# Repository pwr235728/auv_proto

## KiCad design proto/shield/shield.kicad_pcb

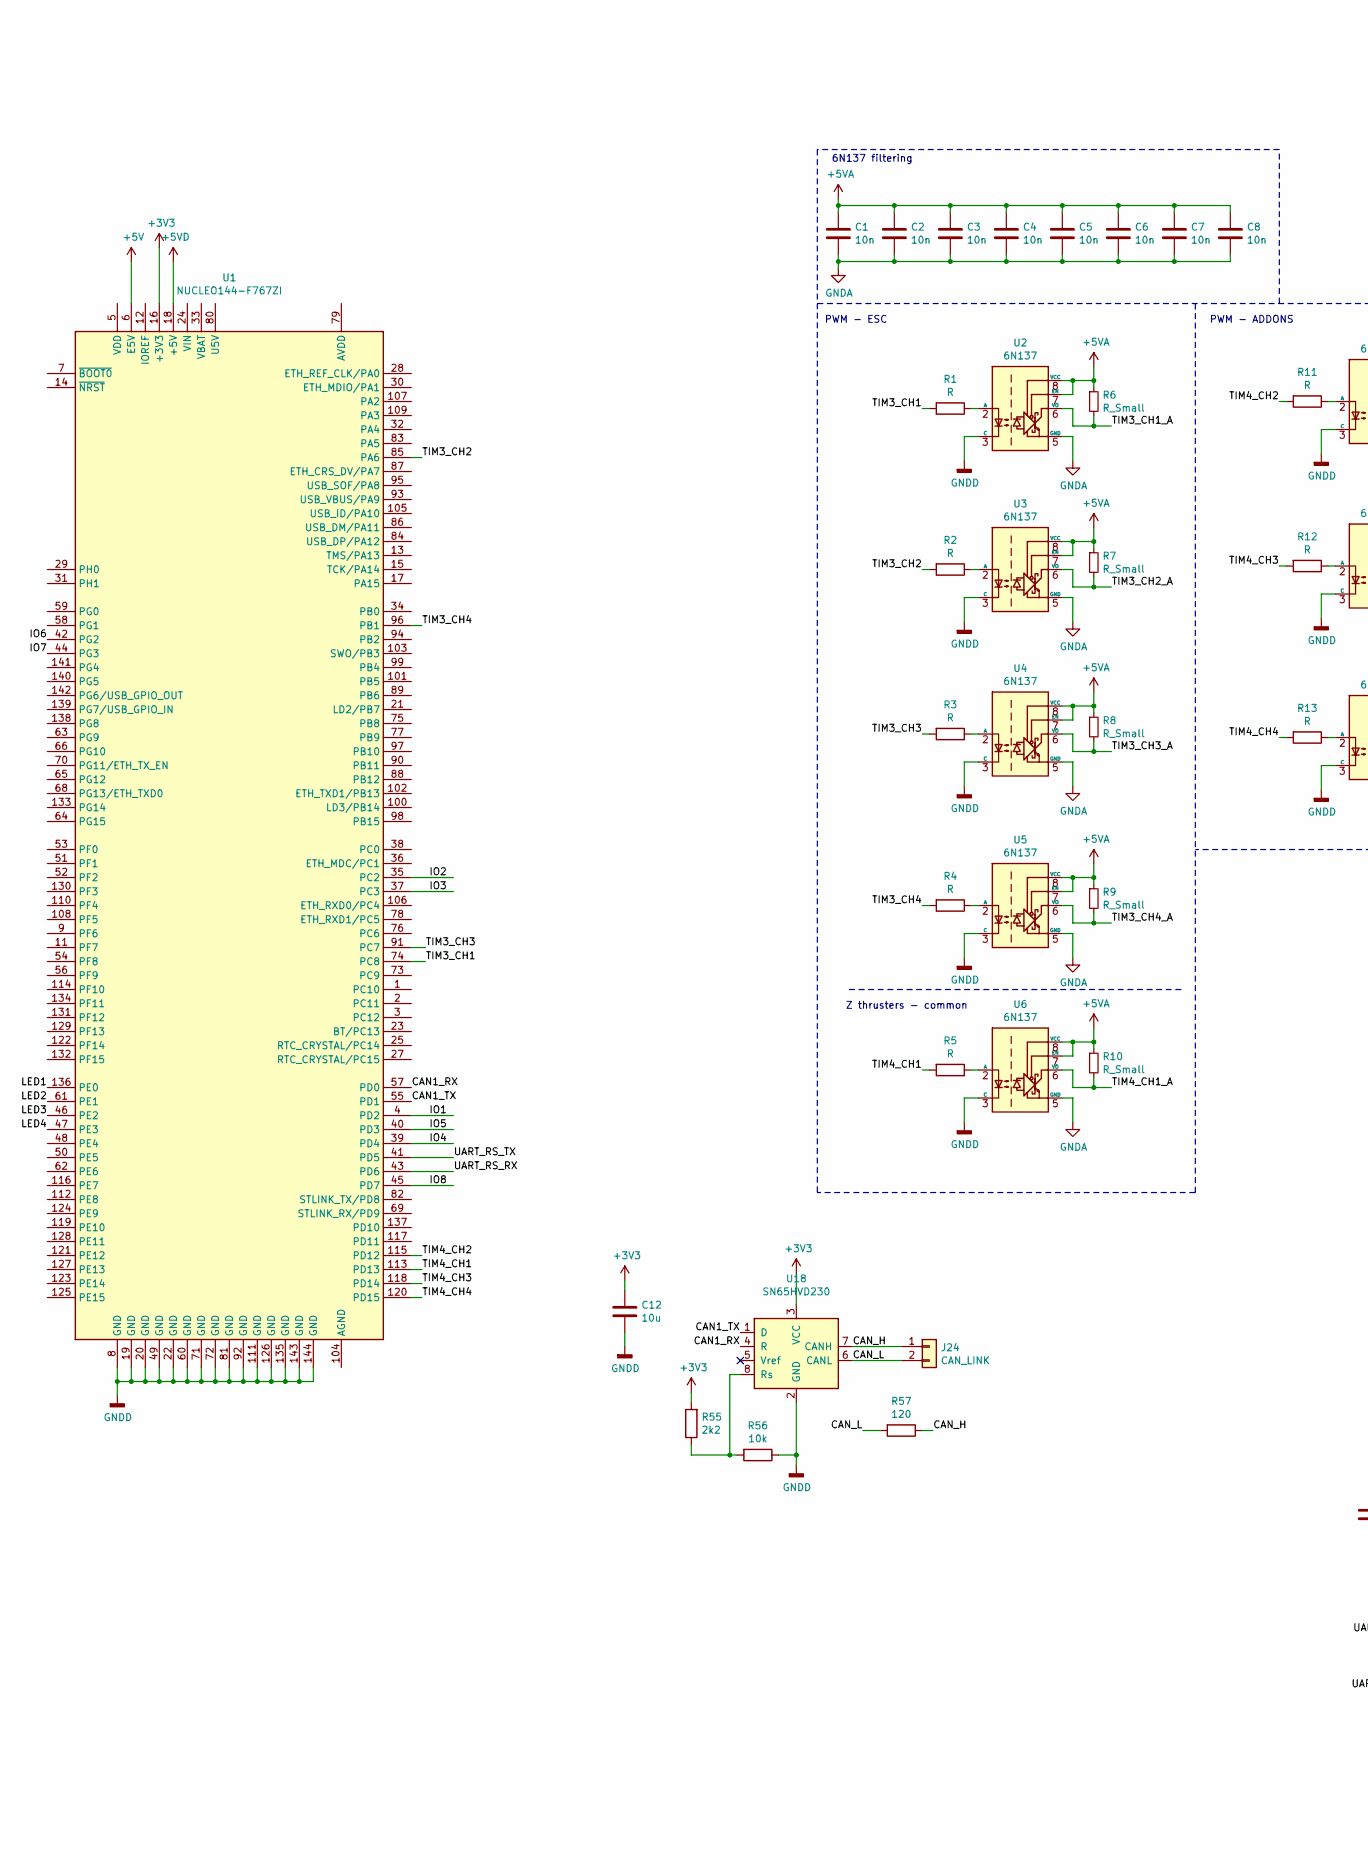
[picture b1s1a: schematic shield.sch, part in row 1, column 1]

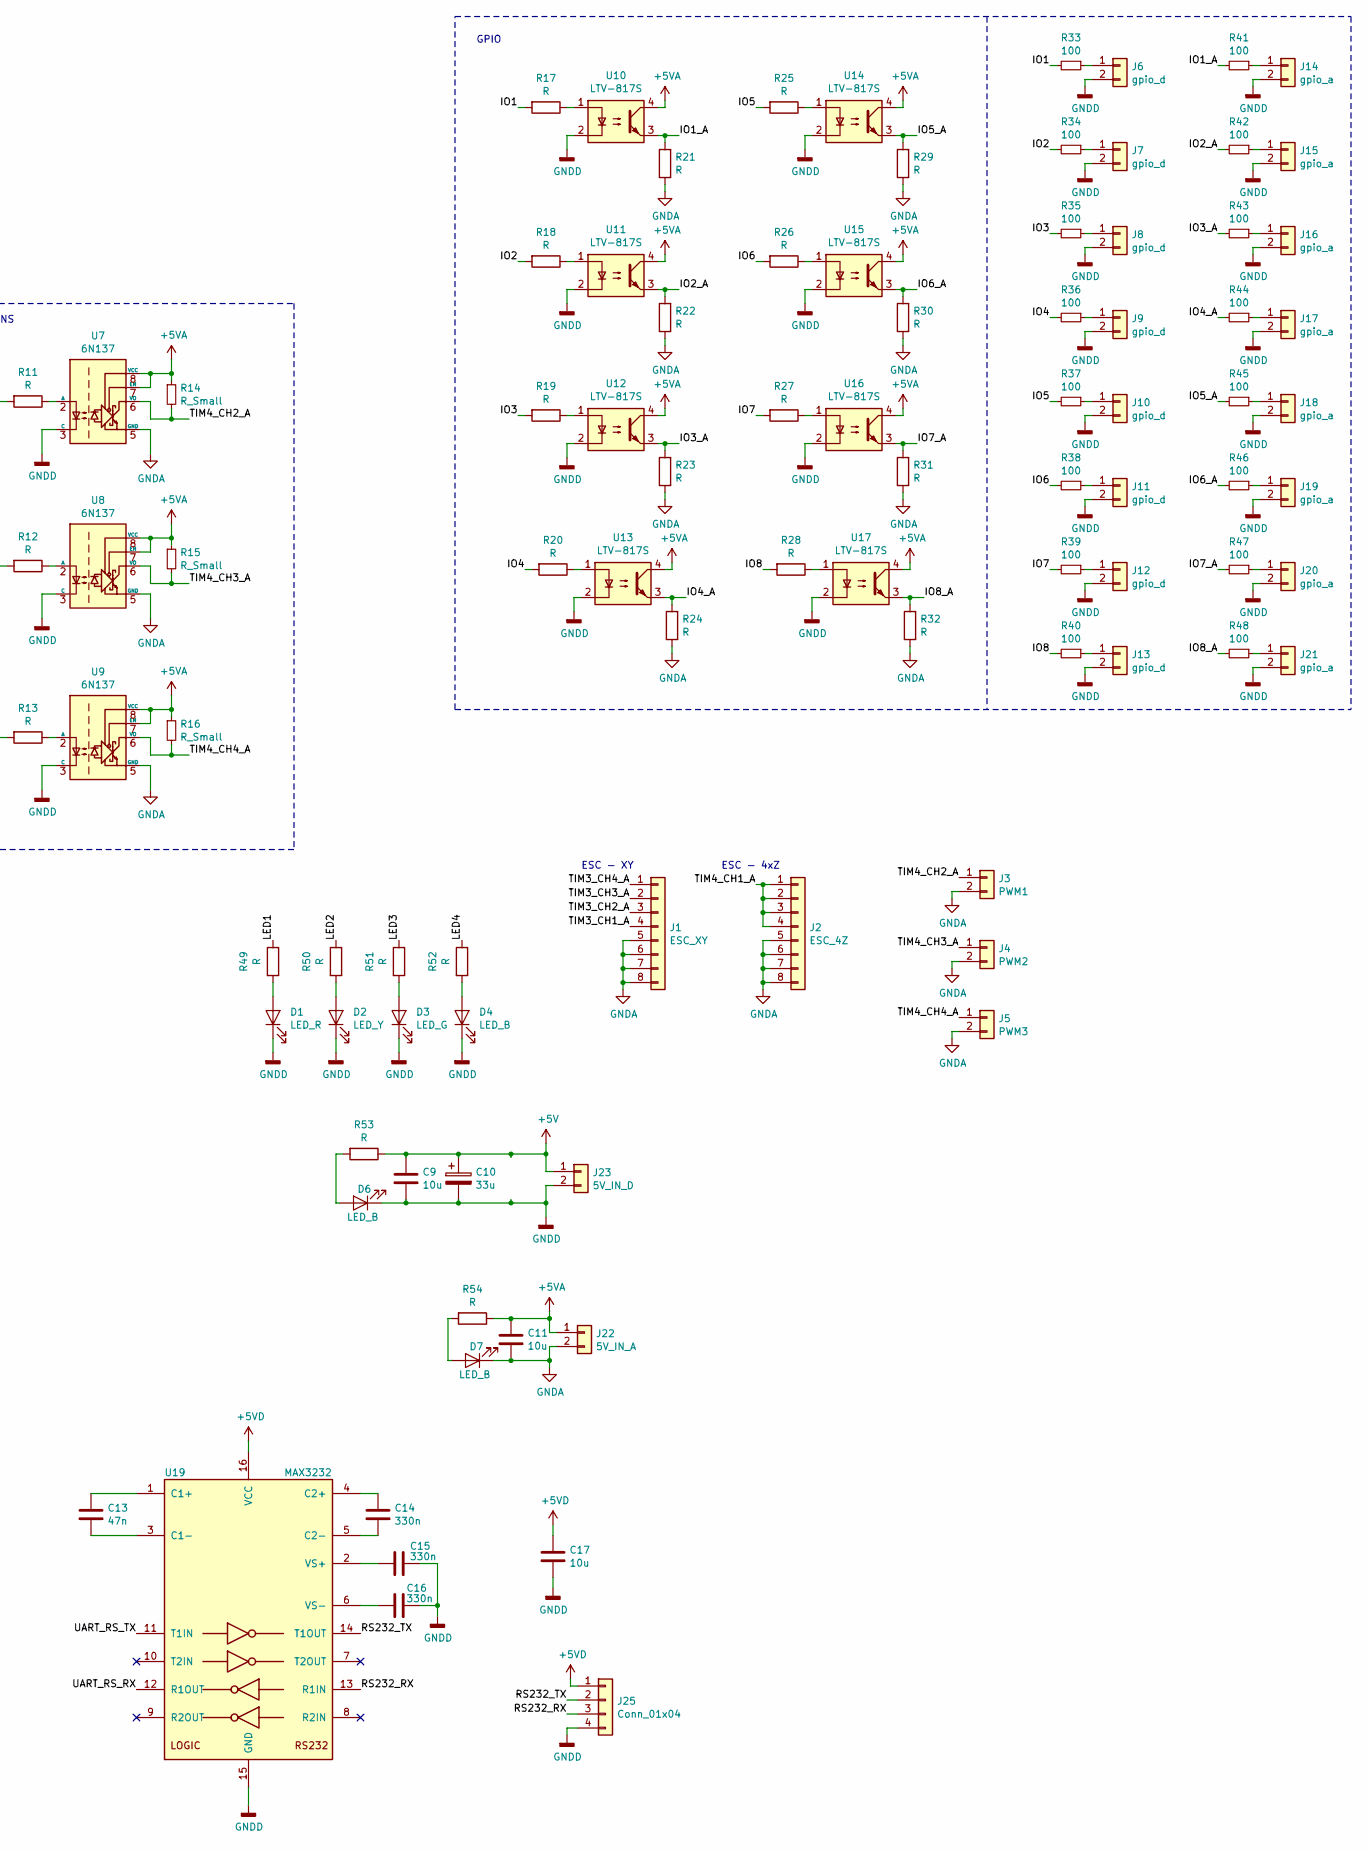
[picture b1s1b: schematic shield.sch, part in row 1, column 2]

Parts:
C1, C2, C3, C4, C5, C6, C7, C8: 10n; C_0805_2012Metric
C9, C11, C12, C17: 10u; C_0805_2012Metric
C10: 33u; CP_EIA-3528-21_Kemet-B
C13: 47n; C_0805_2012Metric
C14, C15, C16: 330n; C_0805_2012Metric
D1: LED_R; LED_0805_2012Metric
D2: LED_Y; LED_0805_2012Metric
D3: LED_G; LED_0805_2012Metric
D4, D6, D7: LED_B; LED_0805_2012Metric
J1: ESC_XY; Molex_SPOX_5267-08A_1x08_P2.50mm_Vertical
J2: ESC_4Z; Molex_SPOX_5267-08A_1x08_P2.50mm_Vertical
J3: PWM1; Molex_SPOX_5267-02A_1x02_P2.50mm_Vertical
J4: PWM2; Molex_SPOX_5267-02A_1x02_P2.50mm_Vertical
J5: PWM3; Molex_SPOX_5267-02A_1x02_P2.50mm_Vertical
J6, J7, J8, J9, J10, J11, J12, J13: gpio_d; JST_PH_B2B-PH-K_1x02_P2.00mm_Vertical
J14, J15, J16, J17, J18, J19, J20, J21: gpio_a; Molex_SPOX_5267-02A_1x02_P2.50mm_Vertical
J22: 5V_IN_A; Molex_Mini-Fit_Jr_5566-02A_2x01_P4.20mm_Vertical
J23: 5V_IN_D; Molex_Micro-Fit_3.0_43650-0215_1x02_P3.00mm_Vertical
J24: CAN_LINK; Molex_MicroClasp_55932-0230_1x02_P2.00mm_Vertical
J25: Conn_01x04; JST_PH_B4B-PH-K_1x04_P2.00mm_Vertical
R1, R2, R3, R4, R5, R11, R12, R13, R17, R18, R19, R20, R21, R22, R23, R24, R25, R26, R27, R28, R29, R30, R31, R32, R49, R50, R51, R52, R53, R54: R; R_0805_2012Metric
R6, R7, R8, R9, R10, R14, R15, R16: R_Small; R_0805_2012Metric
R33, R34, R35, R36, R37, R38, R39, R40, R41, R42, R43, R44, R45, R46, R47, R48: 100; R_0805_2012Metric
R55: 2k2; R_0805_2012Metric
R56: 10k; R_0805_2012Metric
R57: 120; R_0805_2012Metric
U1: NUCLEO144-F767ZI; ST_Morpho_Connector_144_STLink
U2, U3, U4, U5, U6, U7, U8, U9: 6N137; SMDIP-8_W9.53mm
U10, U11, U12, U13, U14, U15, U16, U17: LTV-817S; SMDIP-4_W9.53mm
U18: SN65HVD230; SOIC-8_3.9x4.9mm_P1.27mm
U19: MAX3232; SOIC-16_4.55x10.3mm_P1.27mm

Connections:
+3V3: C12.1, R55.2, U1.16 (+3V3), U18.3 (VCC)
+5V: C9.1, C10.1, J23.1, R53.1, U1.6 (E5V)
+5VA: C1.1, C2.1, C3.1, C4.1, C5.1, C6.1, C7.1, C8.1, C11.1, J22.1, R6.1, R7.1, R8.1, R9.1, R10.1, R14.1, R15.1, R16.1, R54.1, U2.7 (EN), U2.8 (VCC), U3.7 (EN), U3.8 (VCC), U4.7 (EN), U4.8 (VCC), U5.7 (EN), U5.8 (VCC), U6.7 (EN), U6.8 (VCC), U7.7 (EN), U7.8 (VCC), U8.7 (EN), U8.8 (VCC), U9.7 (EN), U9.8 (VCC), U10.4, U11.4, U12.4, U13.4, U14.4, U15.4, U16.4, U17.4
+5VD: C17.1, J25.1, U1.18 (+5V), U19.16 (VCC)
/CAN1_RX: U1.57 (PD0), U18.4 (R)
/CAN1_TX: U1.55 (PD1), U18.1 (D)
/CAN_H: J24.1, R57.1, U18.7 (CANH)
/CAN_L: J24.2, R57.2, U18.6 (CANL)
/IO1: R17.2, R33.2, U1.4 (PD2)
/IO1_A: R21.2, R41.2, U10.3
/IO2: R18.2, R34.2, U1.35 (PC2)
/IO2_A: R22.2, R42.2, U11.3
/IO3: R19.2, R35.2, U1.37 (PC3)
/IO3_A: R23.2, R43.2, U12.3
/IO4: R20.2, R36.2, U1.39 (PD4)
/IO4_A: R24.2, R44.2, U13.3
/IO5: R25.2, R37.2, U1.40 (PD3)
/IO5_A: R29.2, R45.2, U14.3
/IO6: R26.2, R38.2, U1.42 (PG2)
/IO6_A: R30.2, R46.2, U15.3
/IO7: R27.2, R39.2, U1.44 (PG3)
/IO7_A: R31.2, R47.2, U16.3
/IO8: R28.2, R40.2, U1.45 (PD7)
/IO8_A: R32.2, R48.2, U17.3
/LED1: R49.1, U1.136 (PE0)
/LED2: R50.1, U1.61 (PE1)
/LED3: R51.1, U1.46 (PE2)
/LED4: R52.1, U1.47 (PE3)
/RS232_RX: J25.3, U19.13 (R1IN)
/RS232_TX: J25.2, U19.14 (T1OUT)
/TIM3_CH1: R1.2, U1.74 (PC8)
/TIM3_CH1_A: J1.4, R6.2, U2.6 (VO)
/TIM3_CH2: R2.2, U1.85 (PA6)
/TIM3_CH2_A: J1.3, R7.2, U3.6 (VO)
/TIM3_CH3: R3.2, U1.91 (PC7)
/TIM3_CH3_A: J1.2, R8.2, U4.6 (VO)
/TIM3_CH4: R4.2, U1.96 (PB1)
/TIM3_CH4_A: J1.1, R9.2, U5.6 (VO)
/TIM4_CH1: R5.2, U1.113 (PD13)
/TIM4_CH1_A: J2.1, J2.2, J2.3, J2.4, R10.2, U6.6 (VO)
/TIM4_CH2: R11.2, U1.115 (PD12)
/TIM4_CH2_A: J3.1, R14.2, U7.6 (VO)
/TIM4_CH3: R12.2, U1.118 (PD14)
/TIM4_CH3_A: J4.1, R15.2, U8.6 (VO)
/TIM4_CH4: R13.2, U1.120 (PD15)
/TIM4_CH4_A: J5.1, R16.2, U9.6 (VO)
/UART_RS_RX: U1.43 (PD6), U19.12 (R1OUT)
/UART_RS_TX: U1.41 (PD5), U19.11 (T1IN)
GNDA: C1.2, C2.2, C3.2, C4.2, C5.2, C6.2, C7.2, C8.2, C11.2, D7.1 (K), J1.5, J1.6, J1.7, J1.8, J2.5, J2.6, J2.7, J2.8, J3.2, J4.2, J5.2, J22.2, R21.1, R22.1, R23.1, R24.1, R29.1, R30.1, R31.1, R32.1, U2.5 (GND), U3.5 (GND), U4.5 (GND), U5.5 (GND), U6.5 (GND), U7.5 (GND), U8.5 (GND), U9.5 (GND)
GNDD: C9.2, C10.2, C12.2, C15.1, C16.1, C17.2, D1.1 (K), D2.1 (K), D3.1 (K), D4.1 (K), D6.1 (K), J6.2, J7.2, J8.2, J9.2, J10.2, J11.2, J12.2, J13.2, J14.2, J15.2, J16.2, J17.2, J18.2, J19.2, J20.2, J21.2, J23.2, J25.4, R56.1, U1.8 (GND), U1.19 (GND), U1.20 (GND), U1.22 (GND), U1.49 (GND), U1.60 (GND), U1.71 (GND), U1.72 (GND), U1.81 (GND), U1.92 (GND), U1.111 (GND), U1.126 (GND), U1.135 (GND), U1.143 (GND), U1.144 (GND), U2.3 (C), U3.3 (C), U4.3 (C), U5.3 (C), U6.3 (C), U7.3 (C), U8.3 (C), U9.3 (C), U10.2, U11.2, U12.2, U13.2, U14.2, U15.2, U16.2, U17.2, U18.2 (GND), U19.15 (GND)
unnamed: C13.1, U19.1 (C1+)
unnamed: C13.2, U19.3 (C1-)
unnamed: C14.1, U19.4 (C2+)
unnamed: C14.2, U19.5 (C2-)
unnamed: C15.2, U19.2 (VS+)
unnamed: C16.2, U19.6 (VS-)
unnamed: D1.2 (A), R49.2
unnamed: D2.2 (A), R50.2
unnamed: D3.2 (A), R51.2
unnamed: D4.2 (A), R52.2
unnamed: D6.2 (A), R53.2
unnamed: D7.2 (A), R54.2
unnamed: J6.1, R33.1
unnamed: J7.1, R34.1
unnamed: J8.1, R35.1
unnamed: J9.1, R36.1
unnamed: J10.1, R37.1
unnamed: J11.1, R38.1
unnamed: J12.1, R39.1
unnamed: J13.1, R40.1
unnamed: J14.1, R41.1
unnamed: J15.1, R42.1
unnamed: J16.1, R43.1
unnamed: J17.1, R44.1
unnamed: J18.1, R45.1
unnamed: J19.1, R46.1
unnamed: J20.1, R47.1
unnamed: J21.1, R48.1
unnamed: R1.1, U2.2 (A)
unnamed: R2.1, U3.2 (A)
unnamed: R3.1, U4.2 (A)
unnamed: R4.1, U5.2 (A)
unnamed: R5.1, U6.2 (A)
unnamed: R11.1, U7.2 (A)
unnamed: R12.1, U8.2 (A)
unnamed: R13.1, U9.2 (A)
unnamed: R17.1, U10.1
unnamed: R18.1, U11.1
unnamed: R19.1, U12.1
unnamed: R20.1, U13.1
unnamed: R25.1, U14.1
unnamed: R26.1, U15.1
unnamed: R27.1, U16.1
unnamed: R28.1, U17.1
unnamed: R55.1, R56.2, U18.8 (Rs)

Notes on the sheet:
PWM - ADDONS
PWM - ESC
Z thrusters - common
ESC - XY
ESC - 4xZ
6N137 filtering
GPIO

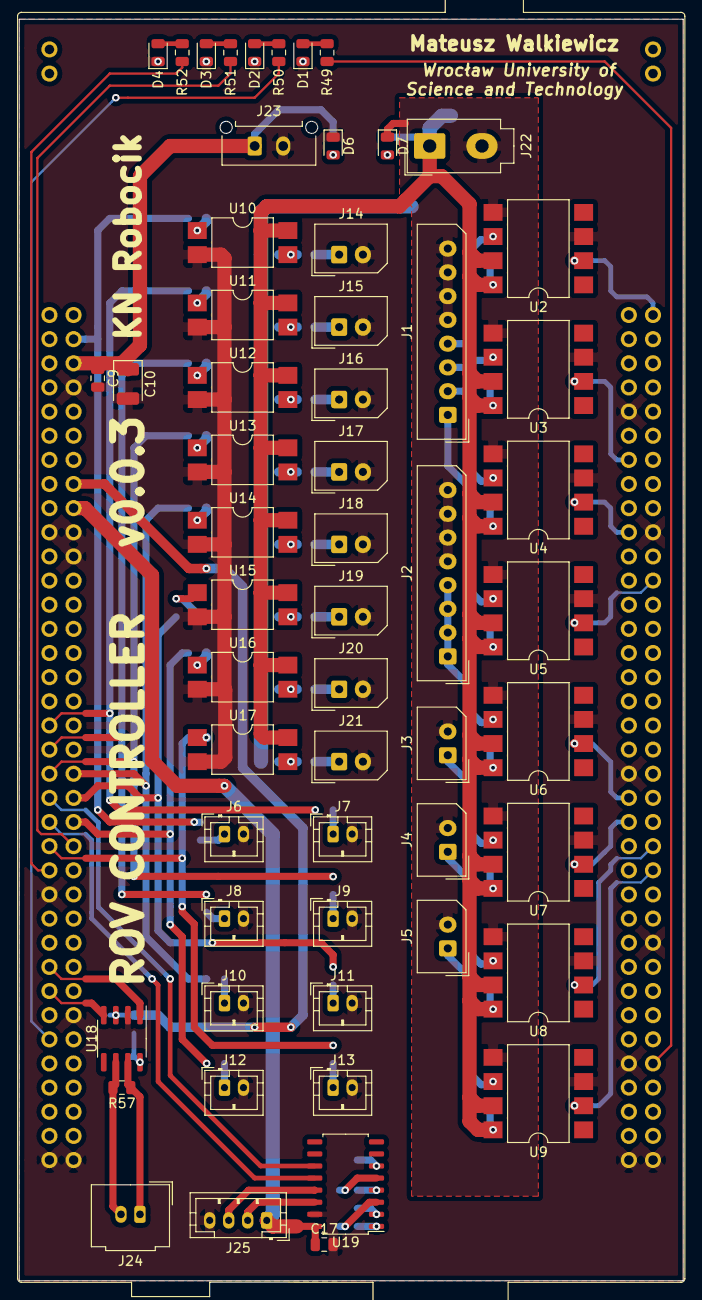
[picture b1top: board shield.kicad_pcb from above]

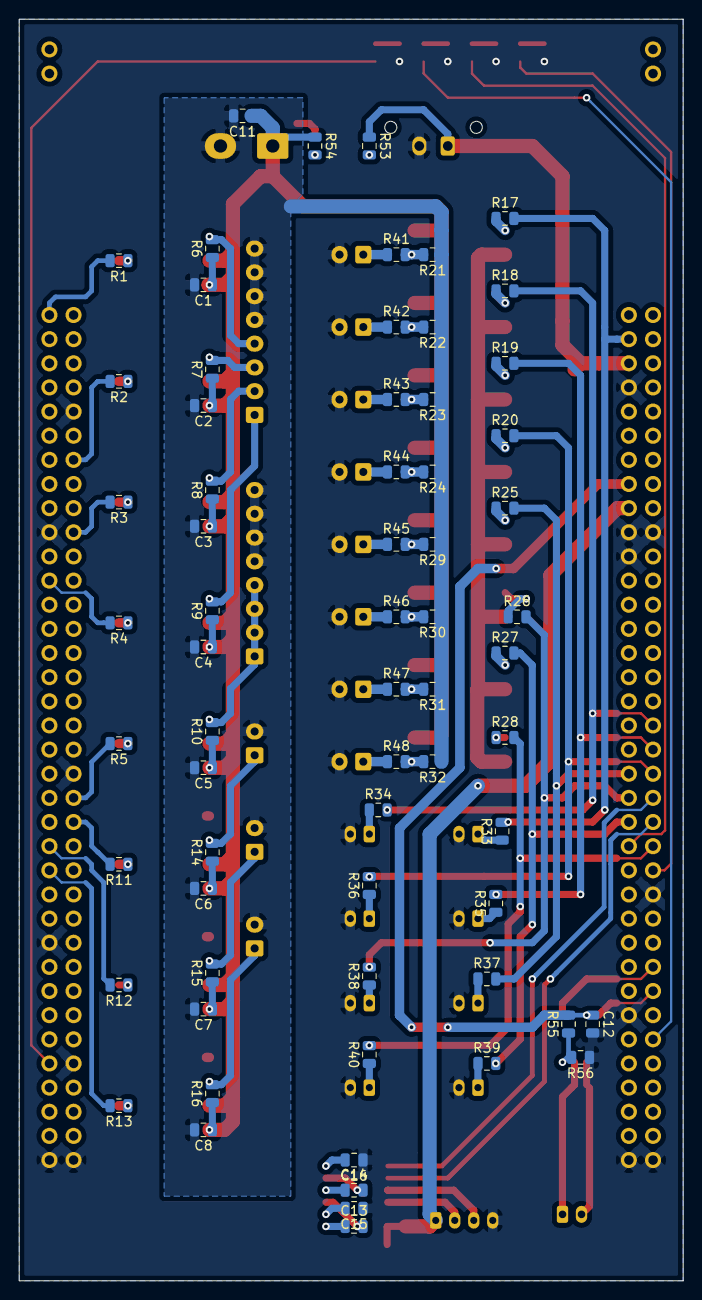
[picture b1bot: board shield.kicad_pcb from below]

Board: 2 copper layers, 69.8 x 132.7 mm, 124 parts (66 on the bottom side), 95 nets.

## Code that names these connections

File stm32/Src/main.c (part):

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  HAL_GPIO_WritePin(GPIOD, GPIO_PIN_0|GPIO_PIN_1|GPIO_PIN_2|GPIO_PIN_3 
                          |GPIO_PIN_4|GPIO_PIN_5|GPIO_PIN_6|GPIO_PIN_7, GPIO_PIN_RESET);

  /*Configure GPIO pins : PE2 PE3 PE0 PE1 */
  GPIO_InitStruct.Pin = GPIO_PIN_2|GPIO_PIN_3|GPIO_PIN_0|GPIO_PIN_1;
  GPIO_InitStruct.Mode = GPIO_MODE_OUTPUT_PP;
  GPIO_InitStruct.Pull = GPIO_NOPULL;
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  GPIO_InitStruct.Pull = GPIO_NOPULL;
  HAL_GPIO_Init(USB_VBUS_GPIO_Port, &GPIO_InitStruct);

  /*Configure GPIO pins : PD0 PD1 PD2 PD3 
                           PD4 PD5 PD6 PD7 */
  GPIO_InitStruct.Pin = GPIO_PIN_0|GPIO_PIN_1|GPIO_PIN_2|GPIO_PIN_3 
                          |GPIO_PIN_4|GPIO_PIN_5|GPIO_PIN_6|GPIO_PIN_7;
  GPIO_InitStruct.Mode = GPIO_MODE_OUTPUT_PP;
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
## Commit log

2019-11-21 Existing files
2019-11-21 Existing files demo_1
2019-11-28 Organizacja katalogów
2019-12-18 Zmiana formatu danych do formatu docelowego
2019-12-19 adding libs directory to repo
2019-12-22 prototyp modułu
2019-12-28 queue for packets with dispatch
2019-12-29 refactoring: PacketQueue api for server <-> tasks communication
2019-12-30 working PacketQueue api
2019-12-30 Dynamic packet_queue_t allocation in function PacketQueue_Create()
2019-12-30 Using a macro to create a module_queue
2019-12-30 Bug fix related to the previous change
2019-12-30 Bug fix in PacketQueue_Create()
2020-01-26 client
2020-01-30 new client base
2020-01-31 pcb + can + rs232
2020-02-01 connectors relocation
2020-02-01 new layout
2020-02-01 pa5->pa6
2020-02-01 finall pcb
2020-02-02 gerber files
2020-02-23 test
2020-02-23 remove old directory
2020-02-23 new idea initial commit xd
2020-02-23 restructure
2020-03-07 `vallen` is verified to be less than `len`, therefore, it can never be the case that `vallen >= len + sizeof(rhostname)`.
    This PR fixes the check so the `rhostname` array does not overflow.
    Reported-by: Github Security Lab <securitylab@github.com>
2020-03-29 Old files
2020-03-30 Working POC. TODO: Dispatcher class
2020-05-07 Add resistors value

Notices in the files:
stm32/Src/main.c:
© Copyright (c) 2019 STMicroelectronics.
All rights reserved.
This software component is licensed by ST under Ultimate Liberty license
(C) COPYRIGHT STMicroelectronics *****END OF FILE
